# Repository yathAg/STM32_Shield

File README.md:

# STM32 Nucleo Shields

The two shields were developed for the STM32G474RE Nucleo64 Board for the Stoch3 Quadraped at IISC Bangalore.

## CAN Shield  

## RS485 Shield

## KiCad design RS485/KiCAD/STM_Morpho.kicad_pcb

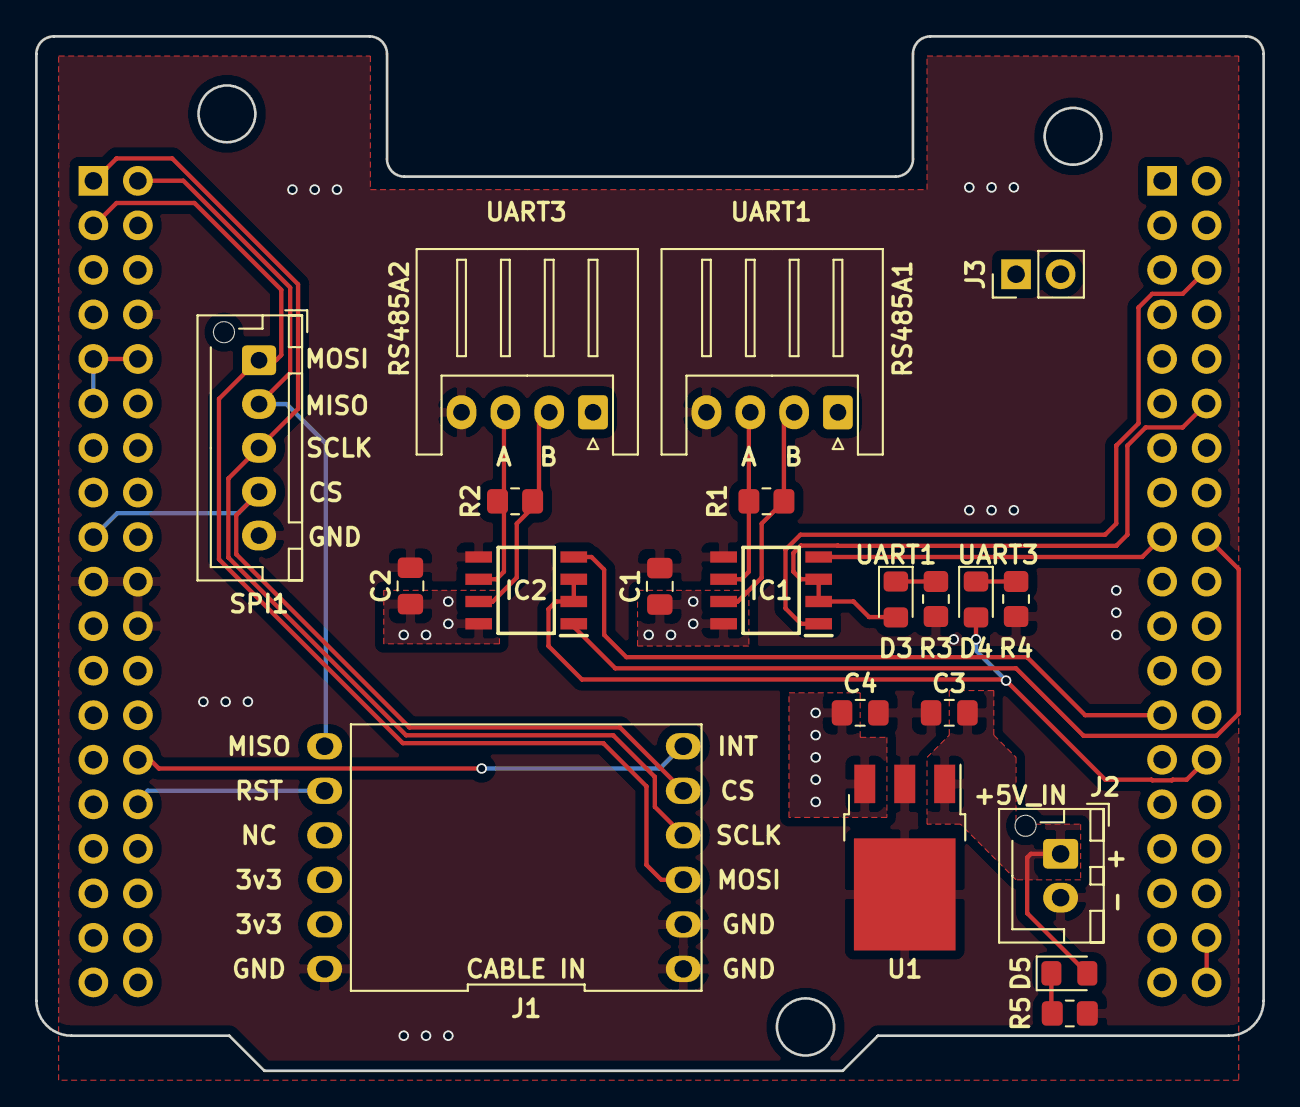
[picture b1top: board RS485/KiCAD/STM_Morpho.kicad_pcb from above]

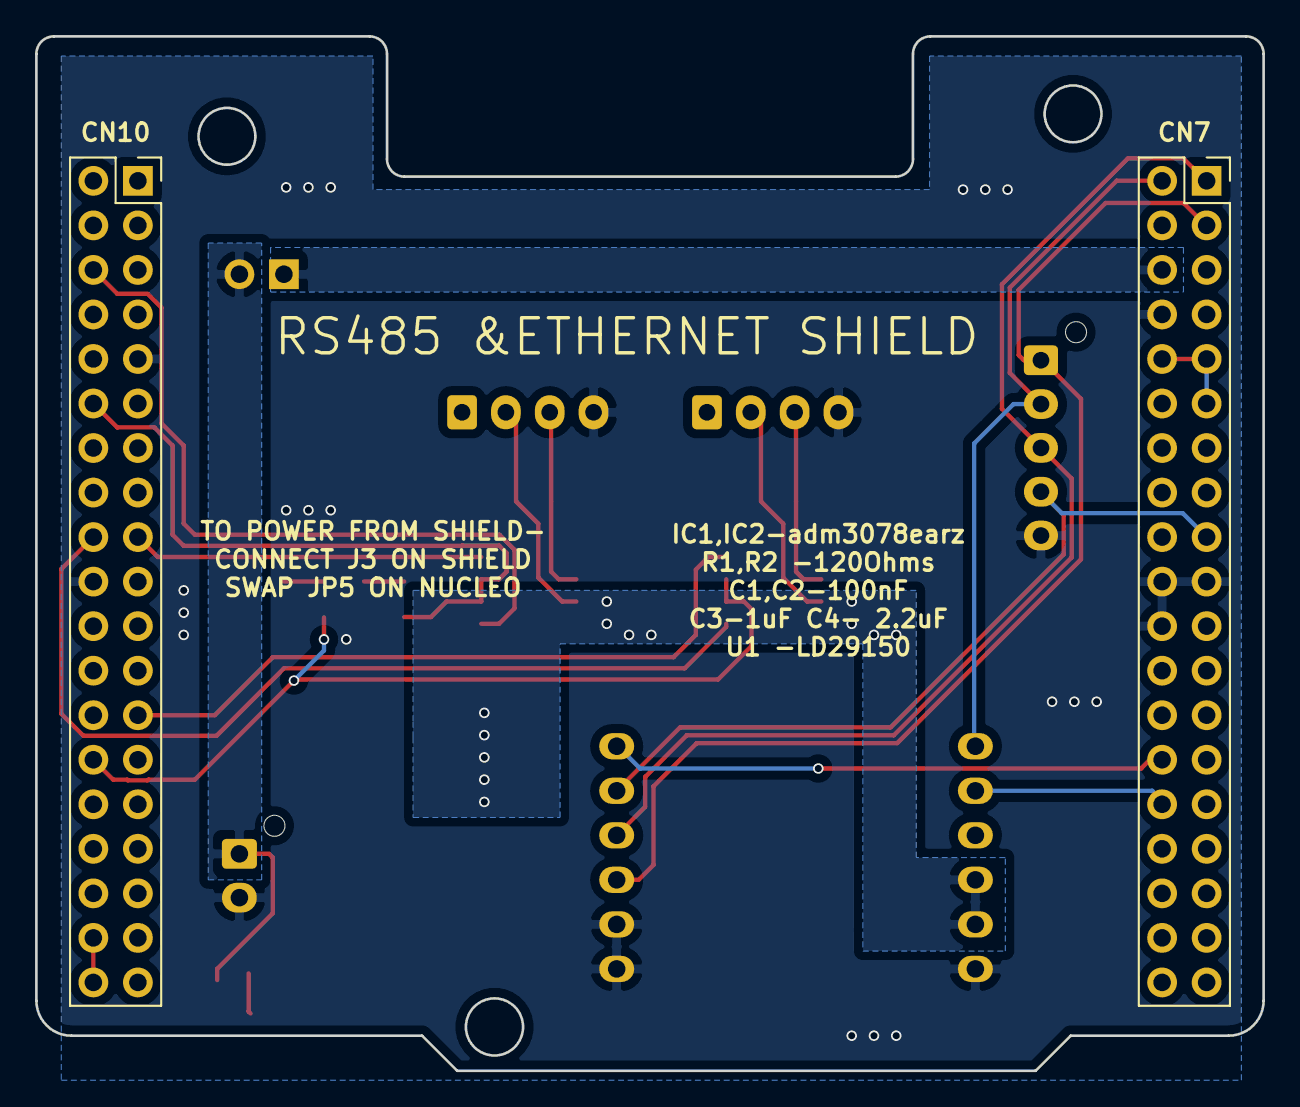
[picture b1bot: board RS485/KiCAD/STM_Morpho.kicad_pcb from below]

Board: 2 copper layers, 70.0 x 59.0 mm, 23 parts (2 on the bottom side), 24 nets.

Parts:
C1, C2: 100nf; C_0805_2012Metric_Pad1.18x1.45mm_HandSolder
C3: 1uf; C_0805_2012Metric_Pad1.18x1.45mm_HandSolder
C4: 2.2uf; C_0805_2012Metric_Pad1.18x1.45mm_HandSolder
CN7, CN10: Conn_02x19_Odd_Even; PinSocket_2x19_P2.54mm_Vertical
D3, D4, D5: LED; LED_0805_2012Metric_Pad1.15x1.40mm_HandSolder
IC1, IC2: ADM3078EARZ; SOIC127P600X175-8N
J1: Conn_02x06_Counter_Clockwise; ethernet_module
J2: Conn_01x02; JST_XH_B2B-XH-AM_1x02_P2.50mm_Vertical
J3: Conn_01x02; PinHeader_1x02_P2.54mm_Vertical
R1, R2: 120; R_0805_2012Metric_Pad1.20x1.40mm_HandSolder
R3, R4, R5: R; R_0805_2012Metric_Pad1.20x1.40mm_HandSolder
RS485A1, RS485A2: Conn_01x04; JST_XH_S4B-XH-A_1x04_P2.50mm_Horizontal
SPI1: Conn_01x05; JST_XH_B5B-XH-AM_1x05_P2.50mm_Vertical
U1: LD39150DT33; TO-252-3_TabPin2

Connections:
+3V3: C1.1, C2.1, C4.1, IC1.8, IC2.8, J1.10, J1.11, U1.3
/NC: CN7.9, CN7.10, CN7.11, CN7.26, CN10.10, CN10.36, CN10.38
E5V: CN7.6, J3.1
GND: C1.2, C2.2, C3.1, C4.2, CN7.8, CN7.19, CN7.20, CN7.22, CN10.9, CN10.20, IC1.5, IC2.5, J1.1, J1.2, J1.12, J2.2, R3.2, R4.2, R5.2, RS485A1.4, RS485A2.4, SPI1.5, U1.2
INT: CN7.28, J1.6
unnamed: D3.1, R3.1
unnamed: D4.1, R4.1
unnamed: D5.1, R5.1
unnamed: IC1.6, R1.2, RS485A1.3
unnamed: IC1.7, R1.1, RS485A1.2
unnamed: IC2.6, R2.2, RS485A2.3
unnamed: IC2.7, R2.1, RS485A2.2
RST: CN7.30, J1.8
SPI_CS: CN7.17, J1.5, SPI1.4
SPI_MISO: CN7.2, J1.7, SPI1.2
SPI_MOSI: CN7.3, J1.3, SPI1.1
SPI_SCLK: CN7.1, J1.4, SPI1.3
UART1_DE: CN10.12, D3.2, IC1.2, IC1.3
UART1_RX: CN10.6, IC1.1
UART1_TX: CN10.17, IC1.4
UART3_DE: CN10.28, D4.2, IC2.2, IC2.3
UART3_RX: CN10.18, IC2.1
UART3_TX: CN10.25, IC2.4
V_IN: C3.2, D5.2, J2.1, J3.2, U1.1

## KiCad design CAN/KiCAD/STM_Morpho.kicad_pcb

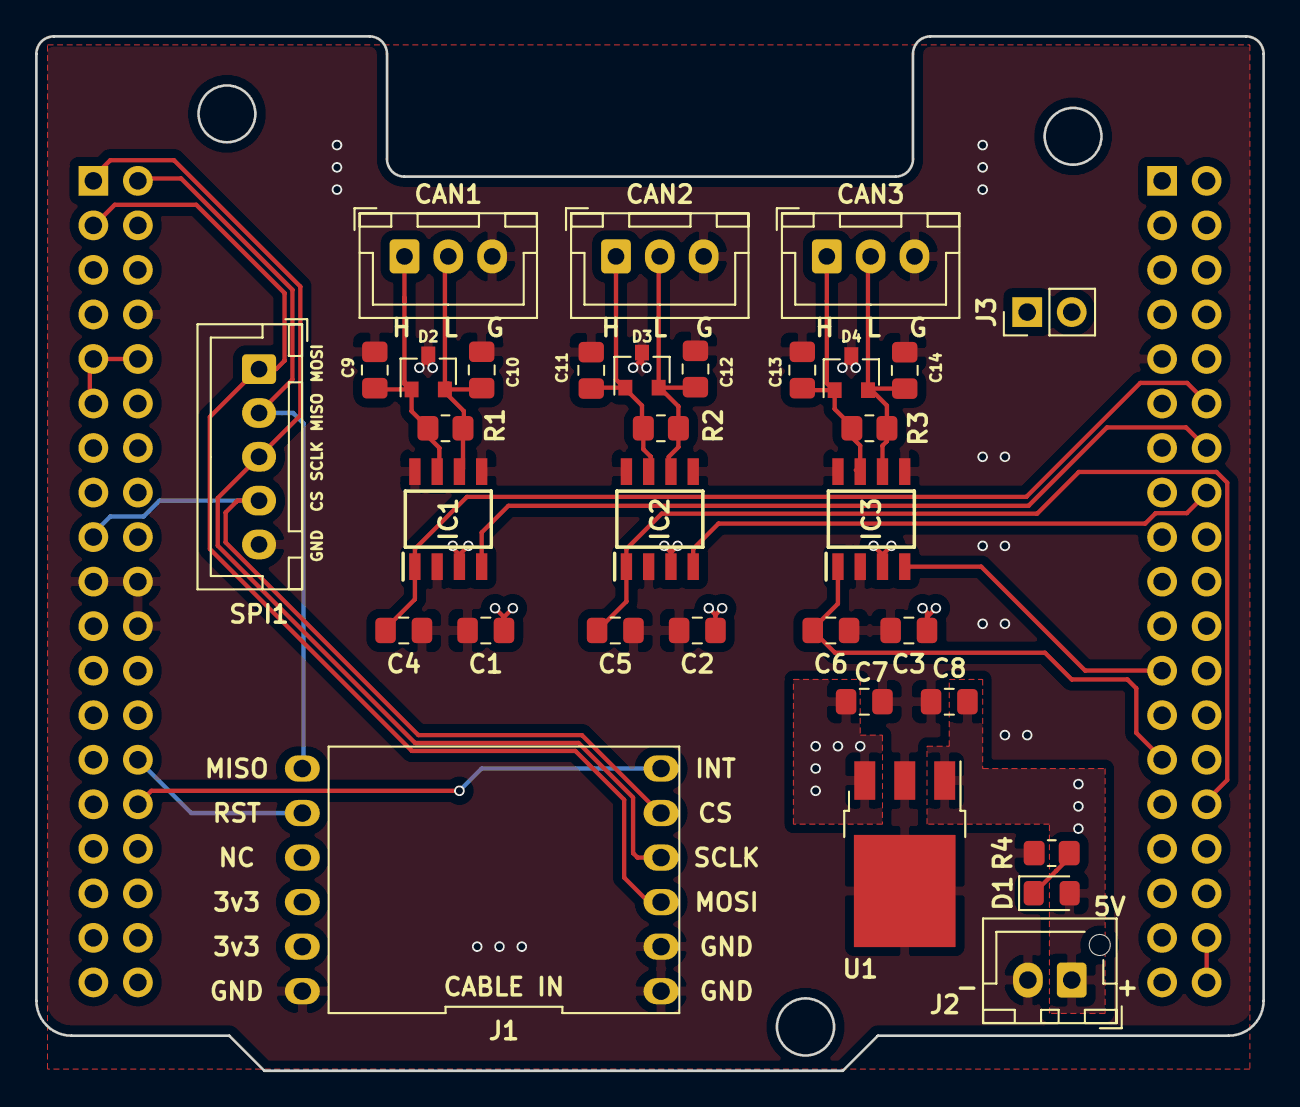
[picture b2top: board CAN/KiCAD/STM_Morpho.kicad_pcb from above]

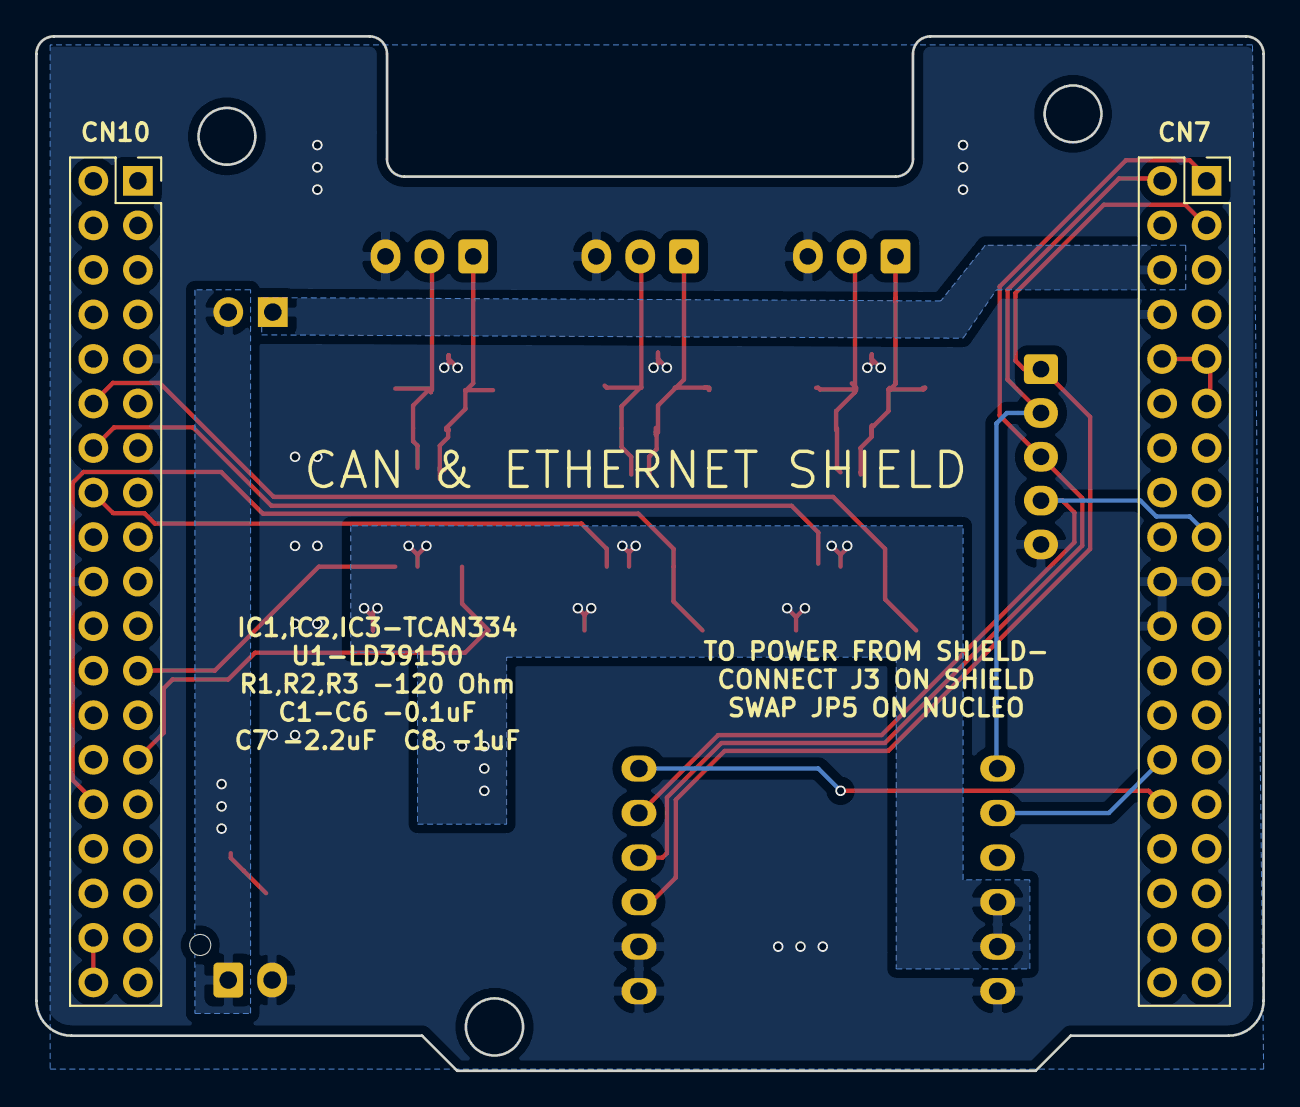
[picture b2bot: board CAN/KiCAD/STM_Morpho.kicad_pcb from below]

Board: 2 copper layers, 70.0 x 59.0 mm, 35 parts (2 on the bottom side), 24 nets.

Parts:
C1, C2, C3: 0.1uf; C_0805_2012Metric_Pad1.18x1.45mm_HandSolder
C4, C5, C6, C9, C10, C11, C12, C13, C14: C; C_0805_2012Metric_Pad1.18x1.45mm_HandSolder
C7: 2.2uf; C_0805_2012Metric_Pad1.18x1.45mm_HandSolder
C8: 1uf; C_0805_2012Metric_Pad1.18x1.45mm_HandSolder
CAN1, CAN2, CAN3: Conn_01x03; JST_XH_B3B-XH-A_1x03_P2.50mm_Vertical
CN7, CN10: Conn_02x19_Odd_Even; PinSocket_2x19_P2.54mm_Vertical
D1: LED; LED_0805_2012Metric_Pad1.15x1.40mm_HandSolder
D2, D3, D4: ESDCAN01; SOT-23
IC1, IC2, IC3: TCAN334GD; SOIC127P600X175-8N
J1: Conn_02x06_Counter_Clockwise; ethernet_module
J2: Conn_01x02; JST_XH_B2B-XH-AM_1x02_P2.50mm_Vertical
J3: Conn_01x02; PinHeader_1x02_P2.54mm_Vertical
R1, R2, R3: 120; R_0805_2012Metric_Pad1.20x1.40mm_HandSolder
R4: R; R_0805_2012Metric_Pad1.20x1.40mm_HandSolder
SPI1: Conn_01x05; JST_XH_B5B-XH-A_1x05_P2.50mm_Vertical
U1: LD39150DT33; TO-252-3_TabPin2

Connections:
+3V3: C1.2, C2.2, C3.2, C7.1, IC1.3, IC2.3, IC3.3, J1.10, J1.11, U1.3
/H1: C9.1, CAN1.1, D2.1, IC1.7, R1.1
/L1: C10.2, CAN1.2, D2.2, IC1.6, R1.2
/NC: CN7.9, CN7.10, CN7.11, CN7.26, CN10.10, CN10.36, CN10.38
E5V: CN7.6, J3.1
FDCAN1RX: CN10.14, IC1.4
FDCAN1TX: C4.1, CN10.12, IC1.1
FDCAN2RX: CN10.16, IC2.4
FDCAN2TX: C5.1, CN10.30, IC2.1
FDCAN3RX: CN10.23, IC3.4
FDCAN3TX: C6.1, CN10.27, IC3.1
GND: C1.1, C2.1, C3.1, C4.2, C5.2, C6.2, C7.2, C8.2, C9.2, C10.1, C11.2, C12.1, C13.2, C14.1, CAN1.3, CAN2.3, CAN3.3, CN7.8, CN7.19, CN7.20, CN7.22, CN10.9, CN10.20, D2.3, D3.3, D4.3, IC1.2, IC1.5, IC1.8, IC2.2, IC2.5, IC2.8, IC3.2, IC3.5, IC3.8, J1.1, J1.2, J1.12, J2.2, R4.1, SPI1.5, U1.2
INT: CN7.30, J1.6
unnamed: C11.1, CAN2.1, D3.1, IC2.7, R2.1
unnamed: C12.2, CAN2.2, D3.2, IC2.6, R2.2
unnamed: C13.1, CAN3.1, D4.1, IC3.7, R3.1
unnamed: C14.2, CAN3.2, D4.2, IC3.6, R3.2
unnamed: D1.1, R4.2
RST: CN7.28, J1.8
SPI_CS: CN7.17, J1.5, SPI1.4
SPI_MISO: CN7.2, J1.7, SPI1.2
SPI_MOSI: CN7.3, J1.3, SPI1.1
SPI_SCLK: CN7.1, J1.4, SPI1.3
V_IN: C8.1, D1.2, J2.1, J3.2, U1.1

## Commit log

2022-09-05 deleted extra files
